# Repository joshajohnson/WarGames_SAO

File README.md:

# SAO
Blinky SAO with a War Games theme.

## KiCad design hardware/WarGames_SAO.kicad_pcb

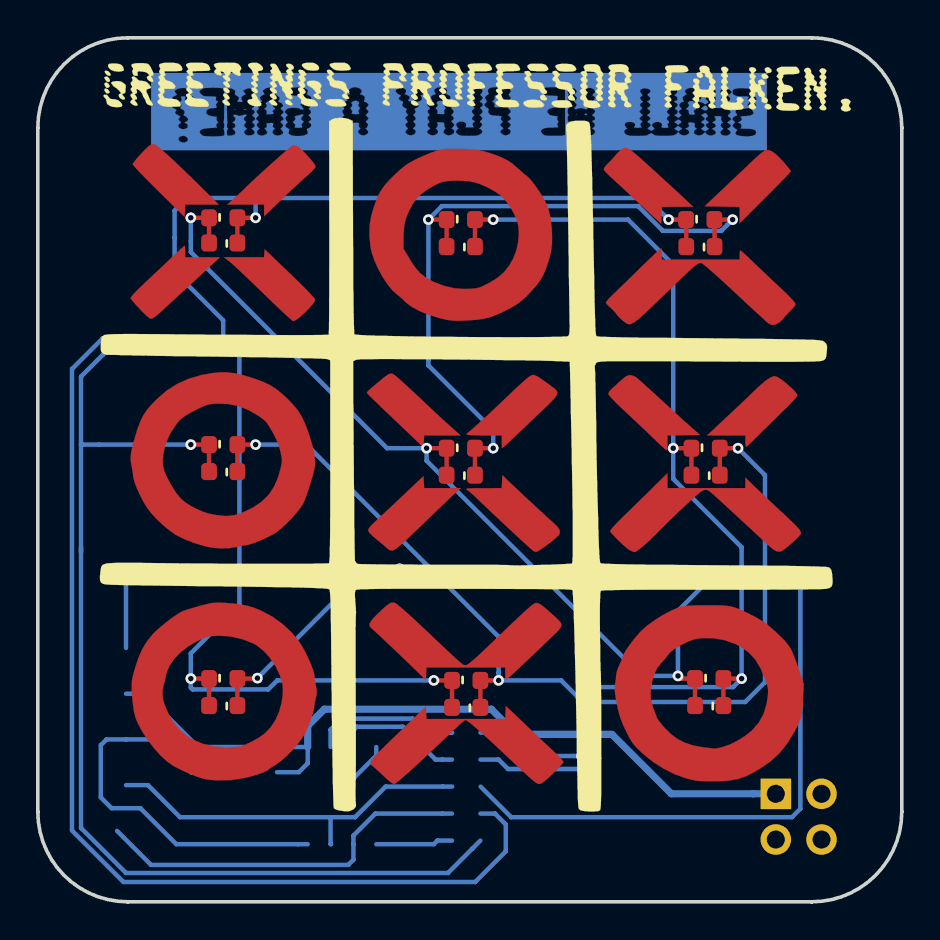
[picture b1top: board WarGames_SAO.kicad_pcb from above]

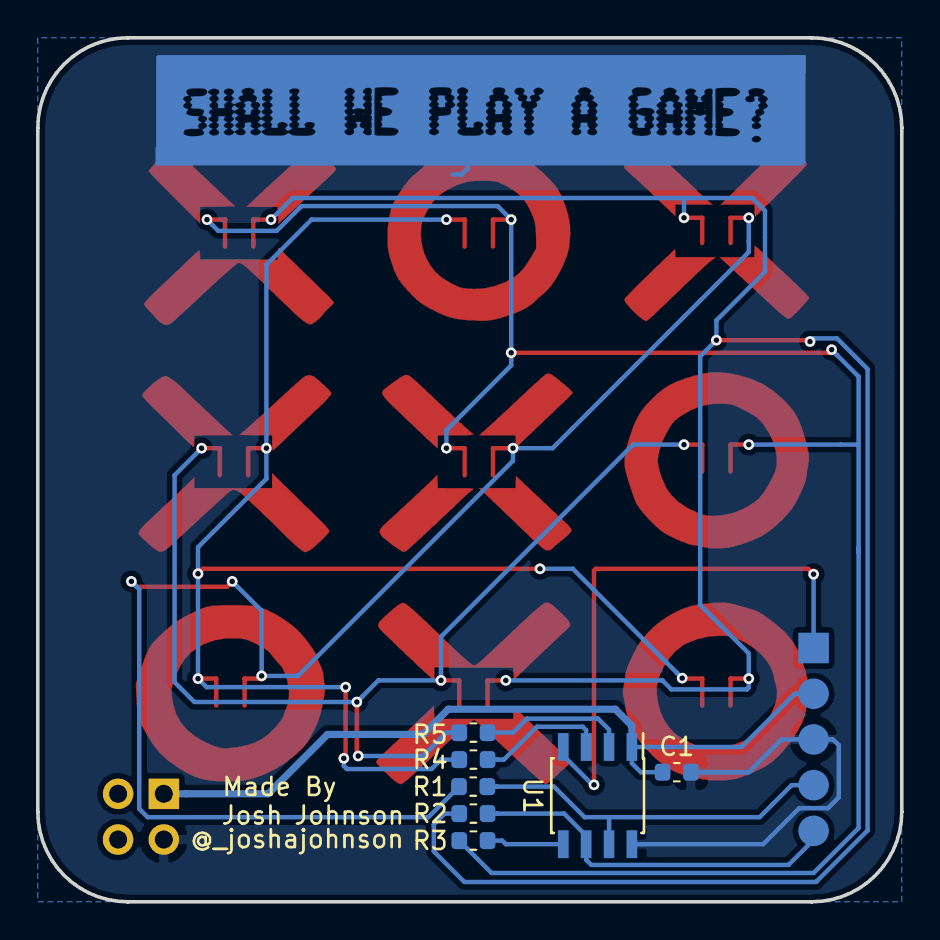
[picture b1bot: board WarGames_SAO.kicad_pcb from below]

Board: 2 copper layers, 48.0 x 48.0 mm, 28 parts (9 on the bottom side), 13 nets.

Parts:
C1: 100n; C_0603_1608Metric
D1, D2, D3, D4, D5, D6, D7, D8, D9, D10, D11, D12, D13, D14, D15, D16, D17, D18: LED; LED_0603_1608Metric
J1: PICKit3_Programmer; PinHeader_1x05_P2.54mm_Vertical
J2: SAO; PinHeader_2x02_P2.54mm_Vertical
R1, R2, R3, R4, R5: 330; R_0603_1608Metric
TP1: Shall We Play A Game?; shall we play a game
U1: PIC12F1571; SOIC-8_3.9x4.9mm_P1.27mm

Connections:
+3V3: C1.1, J1.2, J2.1, U1.1
/ICSPCLK: J1.5, R2.2, U1.6
/ICSPDAT: J1.4, R1.2, U1.7
/RA4: R4.2, U1.3
/RA5: R5.2, U1.2
/nMCLR: J1.1, U1.4
GND: C1.2, J1.3, J2.3, TP1.1, U1.8
unnamed: D1.1, D3.2, D9.1, D10.2, D17.1, D18.2, R1.1
unnamed: D1.2, D3.1, D5.1, D7.2, D13.1, D14.2, D15.1, D16.2, R2.1
unnamed: D2.1, D4.2, D5.2, D7.1, D9.2, D10.1, D11.1, D12.2, R3.1
unnamed: D6.2, D8.1, D11.2, D12.1, D15.2, D16.1, R5.1
unnamed: D2.2, D4.1, D6.1, D8.2, D13.2, D14.1, D17.2, D18.1, R4.1
unnamed: R3.2, U1.5

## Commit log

2019-01-19 init, board laid out and gerbers generated
2019-01-27 Got basic Tic Tac Toe display script working
2019-02-13 Firmware good enough to call it done
2019-03-17 Added schematic in pdf format
